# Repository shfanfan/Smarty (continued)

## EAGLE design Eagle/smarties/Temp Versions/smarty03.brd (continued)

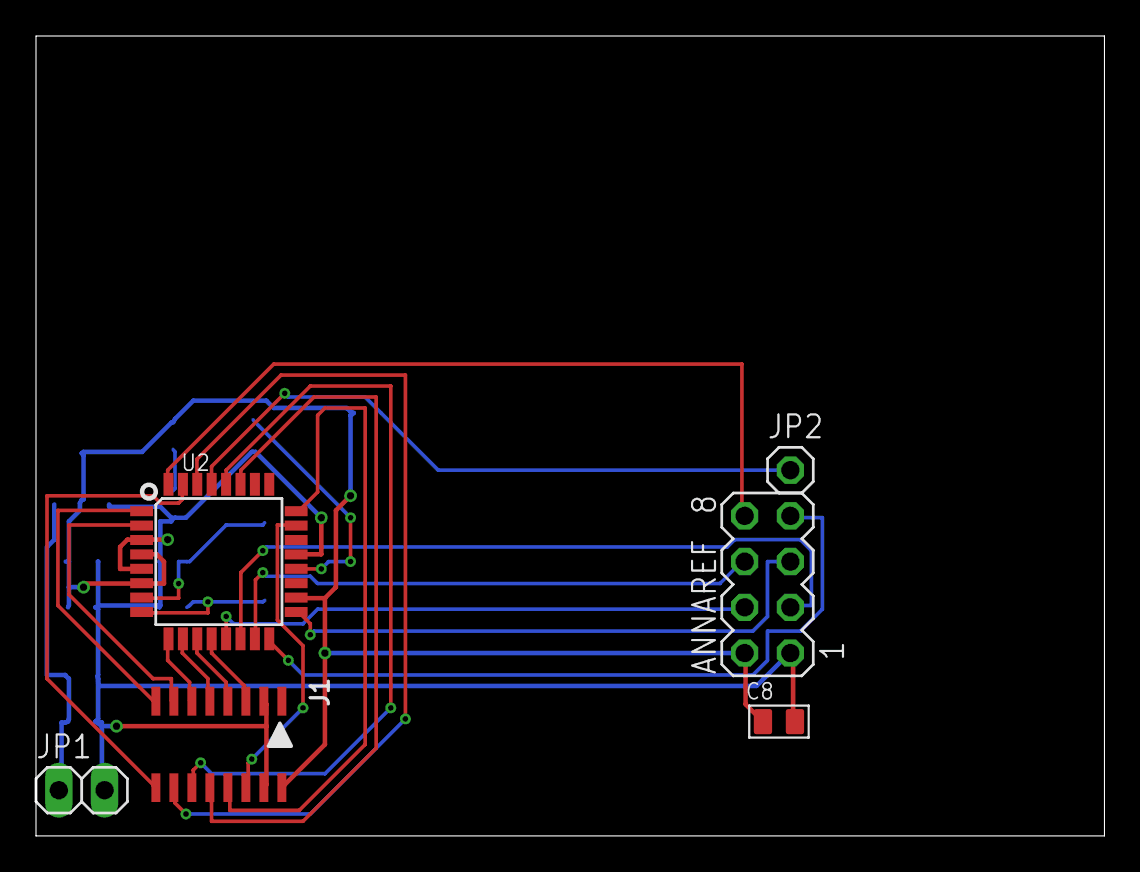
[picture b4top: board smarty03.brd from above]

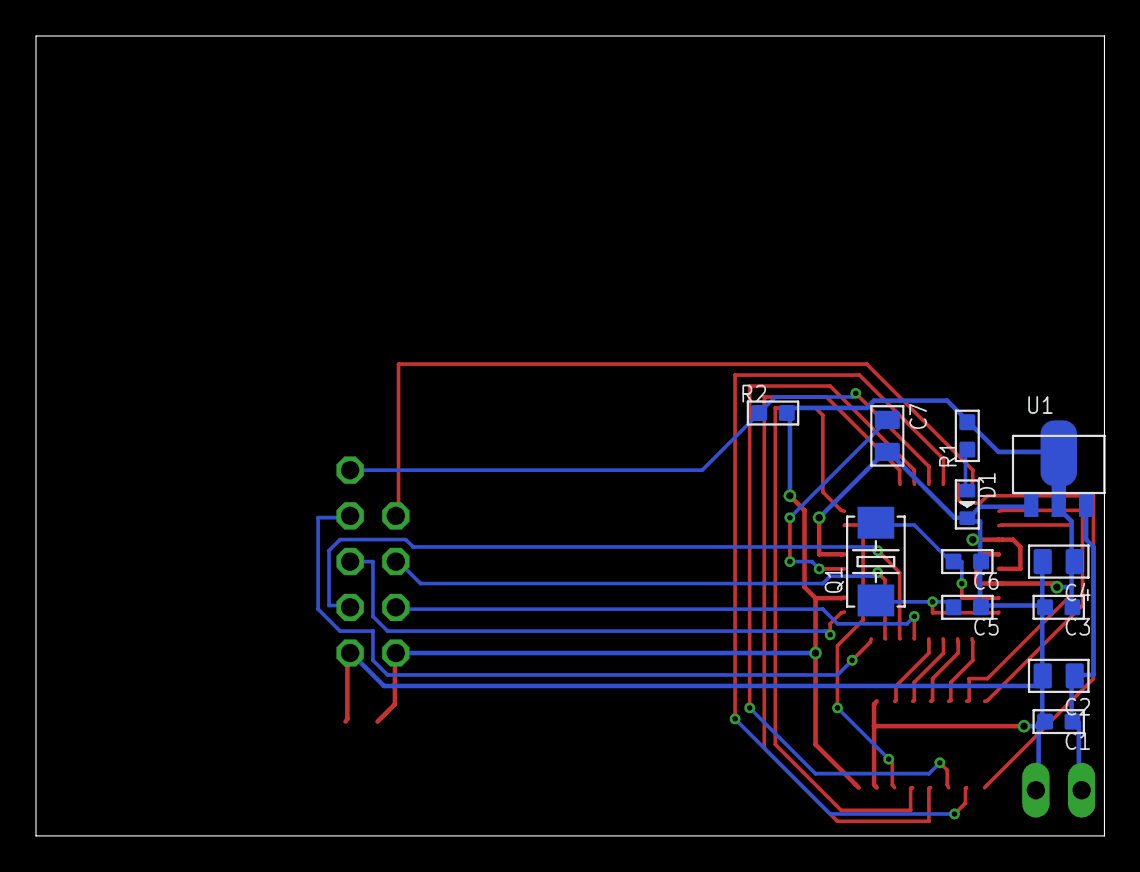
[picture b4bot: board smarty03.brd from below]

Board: 4 copper layers, 59.4 x 44.4 mm, 18 parts (12 on the bottom side), 26 nets.

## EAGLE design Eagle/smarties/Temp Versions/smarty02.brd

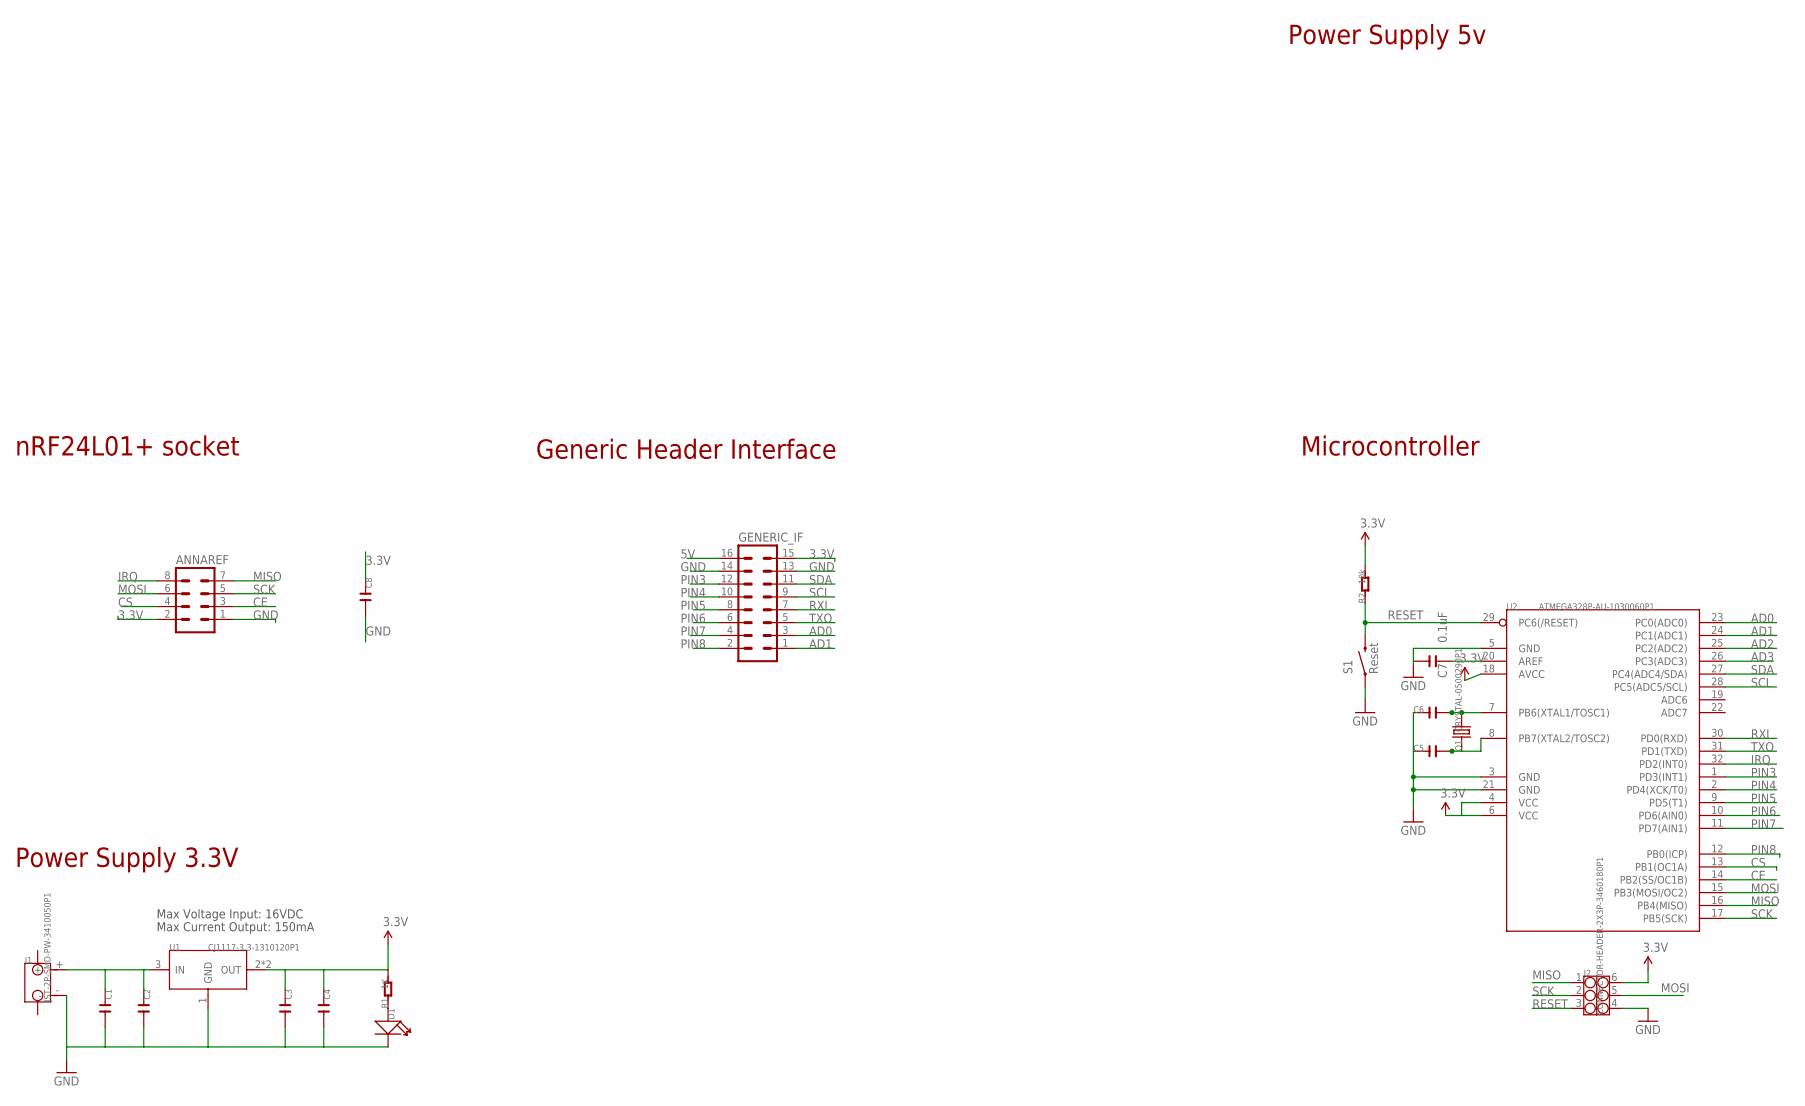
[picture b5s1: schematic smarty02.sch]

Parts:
ANNAREF: MA04-2
C1, C3, C5, C6: C-0603; C0603
C2, C4, C8: C-0805; C0805
C7: 0.1uF; C0805
D1: LED; LED0603
GENERIC_IF: MA08-2
J1: JST-2P-SMD-PW-3410050P1; 2P-SMD-2.0-90D
J2: CONNECTOR-HEADER-2X3P-3460180P1; 2X3P-2.54-2.54-11.6-3.0-BLACK-MALE
Q1: CRYSTAL-0500290P1; 2P-SMD-5.0X3.2
R1: 1K; R0603
R2: 10k; R0603
S1: Reset; TACTILE_SWITCH_SMD
U1: CJ1117-3.3-1310120P1; SOT89
U2: ATMEGA328P-AU-1030060P1; TQFP32

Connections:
3.3V: ANNAREF.2, C3.1, C4.1, C8.1, GENERIC_IF.15, J2.6, R1.2, R2.2, U1.2 (OUT), U1.4 (OUT), U2.4 (VCC), U2.6 (VCC), U2.18 (AVCC)
5V: GENERIC_IF.16
AD0: GENERIC_IF.3, U2.23 (PC0(ADC0))
AD1: GENERIC_IF.1, U2.24 (PC1(ADC1))
AD2: U2.25 (PC2(ADC2))
AD3: U2.26 (PC3(ADC3))
CE: ANNAREF.3, U2.14 (PB2(SS/OC1B))
CS: ANNAREF.4, U2.13 (PB1(OC1A))
GND: ANNAREF.1, C1.2, C2.2, C3.2, C4.2, C5.1, C6.1, C7.2, C8.2, D1.-, GENERIC_IF.13, GENERIC_IF.14, J1.-, J2.4, S1.1, U1.1 (GND), U2.3 (GND), U2.5 (GND), U2.21 (GND)
IRQ: ANNAREF.8, U2.32 (PD2(INT0))
MISO: ANNAREF.7, J2.1, U2.16 (PB4(MISO))
MOSI: ANNAREF.6, J2.5, U2.15 (PB3(MOSI/OC2))
unnamed: C7.1, U2.20 (AREF)
unnamed: C6.2, Q1.2, U2.7 (PB6(XTAL1/TOSC1))
unnamed: C5.2, Q1.1, U2.8 (PB7(XTAL2/TOSC2))
unnamed: D1.+, R1.1
unnamed: C1.1, C2.1, J1.+, U1.3 (IN)
PIN3: GENERIC_IF.12, U2.1 (PD3(INT1))
PIN4: GENERIC_IF.10, U2.2 (PD4(XCK/T0))
PIN5: GENERIC_IF.8, U2.9 (PD5(T1))
PIN6: GENERIC_IF.6, U2.10 (PD6(AIN0))
PIN7: GENERIC_IF.4, U2.11 (PD7(AIN1))
PIN8: GENERIC_IF.2, U2.12 (PB0(ICP))
RESET: J2.3, R2.1, S1.3 (2), U2.29 (PC6(/RESET))
RXI: GENERIC_IF.7, U2.30 (PD0(RXD))
SCK: ANNAREF.5, J2.2, U2.17 (PB5(SCK))
SCL: GENERIC_IF.9, U2.28 (PC5(ADC5/SCL))
SDA: GENERIC_IF.11, U2.27 (PC4(ADC4/SDA))
TXO: GENERIC_IF.5, U2.31 (PD1(TXD))

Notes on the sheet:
Power Supply 3.3V
Microcontroller
Max Voltage Input: 16VDC
Max Current Output: 150mA
Power Supply 5v
Generic Header Interface
nRF24L01+ socket

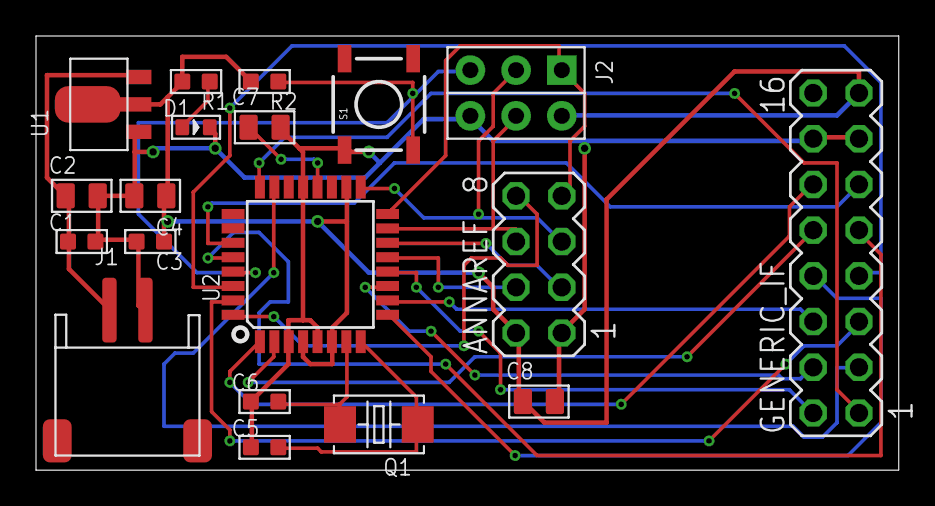
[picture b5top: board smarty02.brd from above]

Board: 4 copper layers, 47.9 x 24.1 mm, 19 parts (0 on the bottom side), 26 nets.

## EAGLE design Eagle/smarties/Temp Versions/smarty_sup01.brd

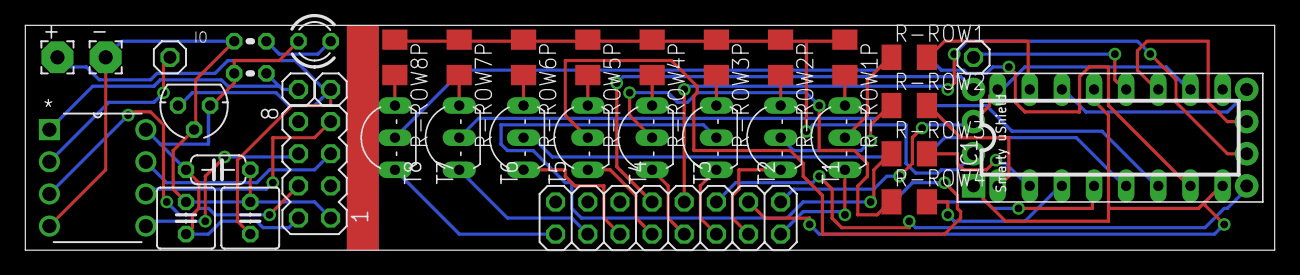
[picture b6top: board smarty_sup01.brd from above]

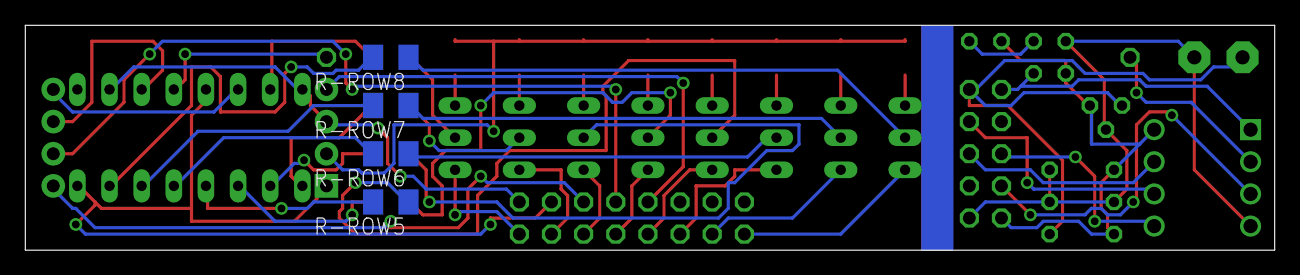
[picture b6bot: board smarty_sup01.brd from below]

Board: 2 copper layers, 98.7 x 17.8 mm, 42 parts (4 on the bottom side), 51 nets.

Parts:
3.3VREG: 78LXX
+: 2,54/1,1
-: 2,54/1,1
ANNAREF3: MA04-2
C11, C12: 10uF; C025-050X050
C13: 100nF; C050-024X044
IC1: 74LS595N; DIL16
IO: 1X01
J1: SMARTY-USHIELD-2.54
JP2: 1X01
JP9: 2X08
LED1: LED3MM
R1: 10k; 0204V
R-LED1: 120; 0204V
R-ROW1, R-ROW2, R-ROW3, R-ROW4, R-ROW5, R-ROW6, R-ROW7, R-ROW8: 4.7k; M1206
R-ROW1P, R-ROW2P, R-ROW3P, R-ROW4P, R-ROW5P, R-ROW6P, R-ROW7P, R-ROW8P: 1k; M1206
RESET1: 1X01
T1, T2, T3, T4, T5, T6, T7, T8: 2N2222; TO92-EBC-OVAL
U1: ATTINY85-20PU; DIP254P762X533-8
VSS1: 1X01

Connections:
85_3V3: 3.3VREG.OUT, ANNAREF3.2, C12.1, C13.2, LED1.A, R1.1, U1.8
85_CS: ANNAREF3.4, U1.3
85_GND: 3.3VREG.GND, -.1, ANNAREF3.1, C11.2, C12.2, C13.1, R-LED1.1, U1.4
85_IO: IO.1, U1.2
85_MISO: ANNAREF3.7, U1.6
85_MOSI: ANNAREF3.6, U1.5
85_RST: R1.2, RESET1.1, U1.1
85_SCK: ANNAREF3.5, U1.7
85_VSS: 3.3VREG.IN, +.1, C11.1, VSS1.1
MX_CLOCK: J1.P5, JP9.5
MX_CLOCK_ROWS: IC1.11, J1.A5
MX_DATA: J1.P3~, JP9.9
MX_DATA_ROWS: IC1.14, J1.A4
MX_GND: IC1.8, IC1.13, J1.UGND, JP9.3
MX_LATCH: J1.P6, JP9.7
MX_LATCH_ROWS: IC1.12, JP2.1
MX_VCC: IC1.10, IC1.16, J1.UVCC, JP9.1
MX_VSS: J1.UVSS, R-ROW1P.1, R-ROW2P.1, R-ROW3P.1, R-ROW4P.1, R-ROW5P.1, R-ROW6P.1, R-ROW7P.1, R-ROW8P.1
unnamed: R-ROW2.1, T2.B
unnamed: R-ROW1.1, T1.B
unnamed: R-ROW1P.2, T1.C
unnamed: R-ROW2P.2, T2.C
unnamed: R-ROW3.1, T3.B
unnamed: R-ROW3P.2, T3.C
unnamed: R-ROW4.1, T4.B
unnamed: R-ROW4P.2, T4.C
unnamed: R-ROW5.1, T5.B
unnamed: R-ROW5P.2, T5.C
unnamed: R-ROW6.1, T6.B
unnamed: R-ROW6P.2, T6.C
unnamed: R-ROW7.1, T7.B
unnamed: R-ROW7P.2, T7.C
unnamed: R-ROW8.1, T8.B
unnamed: R-ROW8P.2, T8.C
unnamed: LED1.K, R-LED1.2
REG-ROW1: IC1.15, R-ROW1.2
REG-ROW2: IC1.1, R-ROW2.2
REG-ROW3: IC1.2, R-ROW3.2
REG-ROW4: IC1.3, R-ROW4.2
REG-ROW5: IC1.4, R-ROW5.2
REG-ROW6: IC1.5, R-ROW6.2
REG-ROW7: IC1.6, R-ROW7.2
REG-ROW8: IC1.7, R-ROW8.2
ROW1: JP9.2, T1.E
ROW2: JP9.4, T2.E
ROW3: JP9.6, T3.E
ROW4: JP9.8, T4.E
ROW5: JP9.10, T5.E
ROW6: JP9.12, T6.E
ROW7: JP9.14, T7.E
ROW8: JP9.16, T8.E

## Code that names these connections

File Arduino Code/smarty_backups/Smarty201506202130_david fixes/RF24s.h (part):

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 *    **ATtiny25/45/85 Pin map with CE_PIN 3 and CSN_PIN 4**
 * @code
 *                                 +-\/-+
 *                   NC      PB5  1|o   |8  Vcc --- nRF24L01  VCC, pin2 --- LED --- 5V
 *    nRF24L01  CE, pin3 --- PB3  2|    |7  PB2 --- nRF24L01  SCK, pin5
 *    nRF24L01 CSN, pin4 --- PB4  3|    |6  PB1 --- nRF24L01 MOSI, pin7
 *    nRF24L01 GND, pin1 --- GND  4|    |5  PB0 --- nRF24L01 MISO, pin6 
 *                                 +----+ 
 * @endcode
 *
 * <br>
 *    **ATtiny25/45/85 Pin map with CE_PIN 3 and CSN_PIN 3** => PB3 and PB4 are free to use for application <br>
 *    Circuit idea from http://nerdralph.blogspot.ca/2014/01/nrf24l01-control-with-3-attiny85-pins.html <br>
 *   Original RC combination was 1K/100nF. 22K/10nF combination worked better.                          <br>
 *	For best settletime delay value in RF24::csn() the timingSearch3pin.ino sketch can be used.         <br>
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 *    Because CE is always high the power consumption is higher than for 5 pins solution                <br>
 * @code
 *                                                                                           ^^         
 *                                 +-\/-+           nRF24L01   CE, pin3 ------|              //         
 *                           PB5  1|o   |8  Vcc --- nRF24L01  VCC, pin2 ------x----------x--|<|-- 5V    
 *                   NC      PB3  2|    |7  PB2 --- nRF24L01  SCK, pin5 --|<|---x-[22k]--|  LED         
 *                   NC      PB4  3|    |6  PB1 --- nRF24L01 MOSI, pin6  1n4148 |                       
 *    nRF24L01 GND, pin1 -x- GND  4|    |5  PB0 --- nRF24L01 MISO, pin7         |                       
 *                        |        +----+                                       |                       
 *                        |-----------------------------------------------||----x-- nRF24L01 CSN, pin4  
 *                                                                      10nF                            
 * @endcode
 *
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 * @code
 *                                  +-\/-+                                                              
 *    nRF24L01  VCC, pin2 --- VCC  1|o   |14 GND --- nRF24L01  GND, pin1
 *                            PB0  2|    |13 AREF
 *                            PB1  3|    |12 PA1
 *                            PB3  4|    |11 PA2 --- nRF24L01   CE, pin3
 *                            PB2  5|    |10 PA3 --- nRF24L01  CSN, pin4
 *                            PA7  6|    |9  PA4 --- nRF24L01  SCK, pin5
 *    nRF24L01 MOSI, pin7 --- PA6  7|    |8  PA5 --- nRF24L01 MISO, pin6
 *                                  +----+
 *	@endcode					 
 *	
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
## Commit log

2016-03-14 first usable code stage
2016-03-14 deleted node modules. one should run "npm install" to get it
2016-03-14 adding ignored files
2016-03-14 added an initial index page in angular2
2016-03-14 some enhancements while learning angular2...
2016-05-01 first client for debugging
2016-09-10 Replace npmcdn.com with unpkg.com
